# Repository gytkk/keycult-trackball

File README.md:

# keycult-trackball

Keycult No.1/60의 기존 케이스를 가공하지 않고 PCB와 알루미늄 보강판을 교체해 G/H 사이에 34mm 트랙볼을 통합하는 개인 프로젝트입니다. 제작 시제품은 cocot36plus를 참고한 베어링 롤러와 수평 PMW3360 모듈, 62키 직교 배열을 사용합니다. 유선 USB에서 키보드와 포인팅 장치를 함께 처리하는 QMK 펌웨어를 빌드했으며 실물 동작은 아직 시험하지 않았습니다.

현재 작업 위치는 비공개 독립 저장소 [gytkk/keycult-trackball](https://github.com/gytkk/keycult-trackball)입니다. 명령은 이 저장소 루트에서 실행합니다. 공개 선행 저장소 [gytkk/keycult-ball](https://github.com/gytkk/keycult-ball)은 별도로 유지하며 이 프로젝트의 변경을 그곳에 푸시하지 않습니다.

모노레포의 `8649717d63becea25a07a4f4efe33436537c2d38` 시점 산출물과 프로젝트 전용 변경 이력을 이전했습니다. 최초 파일 반입 트리가 선행 저장소의 `e3069346080183b74a5486131bdb68340fdf376d` 트리와 같아 해당 원본 이력에 후속 변경을 연결했습니다. 원본 추출 이력은 `archive/monorepo-extraction`, 선행 저장소 기준점은 `archive/keycult-ball-main` 브랜치에 보존합니다. 기존 이슈 링크는 선행 저장소의 기록을 가리키며 생성 보고서의 과거 절대 경로도 출처 기록으로 유지합니다.

현재 개발 우선안은 **62키 배열과 알루미늄 보강판**입니다. 65키안은 비교용으로 유지합니다. 시제품은 1.5mm 6061-T6 알루미늄 판재와 버 제거를 선택하며 가공 공차와 실제 강성은 검증이 필요합니다. [중앙 PCB 개구 검토](design/preliminary/design.md#중앙-pcb-개구와-알루미늄-보강판)에서 제조 방식과 남은 설계 조건을 설명합니다.

[출력용 홀더 시제품](design/printable-holder/README.md)은 **PCB 아래 0.82mm까지만 공간이 있다는 가정**으로 설계합니다. 이는 짧은 Mill-Max 3305-0의 명목 돌출을 참고한 사용자 요청이며 실제 케이스 측정값이 아닙니다. 받침을 보강판 위에 놓고 센서를 올려, 나사까지 포함한 하부 돌출을 PCB 아래 0.4mm로 제한합니다. 볼 중심은 보강판 위 23.5mm, 위끝은 40.5mm이므로 높은 볼의 사용성은 출력 후 확인해야 합니다. 상부 링은 없으며 볼을 위로 들어낼 수 있습니다. [단면도](design/preliminary/section.png)와 [치수 근거](design/preliminary/sources/README.md#shallow-clearance-reference)를 함께 확인합니다.

62키 DRAFT H는 모든 실장 전자부품을 PCB 윗면으로 옮기고 중앙 뒤쪽에 MCU, 전원과 커넥터를 배치합니다. 48 x 48mm R1 중앙 PCB 개구, 36 x 36mm R3 보강판 창과 42mm 체결 피치를 사용합니다. [PCB 안내](design/pcb/README.md)의 Gerber, PTH/NPTH 드릴, BOM과 실장 좌표는 시제품 제작 검토용이며 [검증 보고서](design/pcb/62/reports/validation.json)와 같은 원본에서 생성합니다. [펌웨어 안내](firmware/README.md)에 실제 UF2 빌드 결과와 입력 기능, 재현 및 초기 전원 시험 조건이 있습니다. 출력물, 실제 센서, 케이블과 케이스를 함께 조립한 검증은 남아 있습니다.

보유 케이스는 NovelKeys 최신 판매 버전의 WK이며 정확한 리비전과 과거 공식 보강판 윤곽의 호환성은 확인이 필요합니다. 이번 시제품의 장치와 배열은 cocot 방식과 62키로 선택했습니다. [과거 대안 조사](docs/feasibility.md)는 참고 자료로 유지하며 실제 장착 공간을 대신하지 않습니다.

현재 홀더에 맞춘 보강판과 조립 CAD는 [홀더 안내](design/printable-holder/README.md)와 [재현 절차](docs/reproduction.md#출력용-독립-홀더-시제품)를 따릅니다. 공식 NoLeaf 외곽을 포함하는 STEP/DXF/FCStd는 `design/preliminary/sources/local/`에만 생성합니다. 공개 홀더 CAD의 직사각형 `CandidatePlate`는 실제 Keycult 가공용 보강판이 아닙니다. 이전 65키 및 깊은 62키 보강판 검토는 과거 비교용입니다.

[케이스를 포함한 FreeCAD 참조 모델](design/preliminary/design.md#케이스-참조-모델)은 기존 홀더 검토 사본에 공개 외장 치수와 가정한 내부 형상을 추가합니다. 65키와 62키의 반투명 전체 보기, 절개 보기와 객체별 간섭 결과를 로컬에 생성하며 [실행 방법](docs/reproduction.md#케이스-참조-형상을-포함한-freecad-검토)을 따릅니다. 실제 케이스 내부와 보강판 정렬은 실측하지 않았으므로 참조 모델의 간섭 결과를 실물 조립 판정으로 사용하지 않습니다.

## 현재 검토 중인 배치

우선안은 15u 너비의 5행 62키 배열이며, 중앙 3열의 위쪽 4행을 비워 트랙볼과 뒤쪽 센서 공간을 확보합니다. 하단 중앙은 1.5u M1/M2 두 키로 총 3u를 차지하며 M3 물리 키는 제거합니다. 실제 키캡과 스위치 조립 적합성은 미확정입니다. 아래 값은 현재 예비 설계의 계산값입니다.

| 항목 | 값 또는 조건 |
| --- | --- |
| 키 피치와 명목 키필드 | 19.05mm, 285.75 × 95.25mm |
| 볼과 G/H 키 중심 | 볼 `(0, 0)`, G `(-38.10, 0)`, H `(+38.10, 0)`, 단위 mm |
| 볼과 키캡 사이 최소 평면 간격 | 지름 34mm 볼과 1u 18 x 18mm, 1.5u 27.525 x 18mm 키캡 가정에서 12.10mm |
| 임시 조립 예약 영역 | 50 × 50mm, 키캡과 최소 4.10mm 간격 |
| 개발 우선안 | 15u 62키. 65키안의 상단 중앙 Vol-/Mute/Vol+를 제거해 중앙 명목 빈 영역을 57.15 × 76.20mm로 확장 |
| 보류한 대안 | 14u 너비의 64키 배열. 같은 예약 영역과 키캡이 5.425mm 겹침 |

62키안은 볼 지름 34mm와 중심, G/H 및 하단 1.5u M1/M2를 포함한 나머지 키를 유지합니다. 뒤쪽 한 행을 비워 센서와 배선, 지지 브리지와 체결 간격을 검토할 공간을 확보합니다. 키 제거만으로 강성이 좋아지는 것은 아니며, 빈 영역 전체를 절개하면 강성이 낮아질 수 있습니다. 볼 지름은 65키안과 같지만 현재 62키 홀더의 하부 센서 공간은 별도로 검토합니다.

KiCad 원본은 비교용 65키의 `design/pcb/keycult65.*`와 제작 시제품 62키의 `design/pcb/62/keycult62.*`로 나눕니다. 62키는 윗면 전자부품을 뒤쪽 중앙 빈 영역에 배치하며 중앙 개구에서 0.25mm 확장한 영역을 구리와 부품 금지 영역으로 사용합니다. 개구, 높이와 커넥터는 시제품 설계값이며 실제 센서 및 케이스와 대조해야 합니다. 키 좌표는 예비 배치, PCB와 펌웨어가 공유합니다.

50 × 50mm 영역은 실제 홀더 외곽이나 보강판 및 PCB의 가공 구멍 치수가 아닙니다. 공개 도면의 초록색 경계도 공식 보강판 윤곽을 복제한 것이 아니라, 전체 치수만 참조한 285.75 × 108.25mm 직사각형입니다. 현재 검증은 이 경계 안의 포함 여부와 부품 사이 평면 간격을 확인하며, 실제 케이스 개구부 통과나 수직 공간, 조립 가능 여부를 증명하지 않습니다.

## 자료 안내

| 자료 | 내용 |
|---|---|
| [프로젝트 맥락](docs/project-context.md) | 요구사항, 결정 이유, 확정/가정/미확정, 실측·다음 단계 |
| [KiCad 65키·62키 초안](design/pcb/README.md) | 각 배열의 편집 가능한 회로도·PCB, BOM·GPIO 맵, 실제 ERC/DRC·좌표 검증 및 PDF/SVG |
| [PCB 구현 계획](docs/pcb-implementation-plan.md) | 실측 전에 진행할 회로도·PCB 초안, 단계별 산출물과 제조 전 검증 |
| [62키 QMK 펌웨어](firmware/README.md) | 빌드한 UF2, 고정된 소스, 버튼과 스크롤 기능, 재현 및 초기 동작 시험 |
| [실현 가능성과 대안 조사](docs/feasibility.md) | 34mm 중앙 통합의 제약과 중앙에 통합할 소형 터치패드·트랙볼 비교 |
| [상세 설계와 출처](design/preliminary/design.md) | 치수 계산, 장착·flex, 센서 방향, QMK·USB 범위 |
| [Ploopy / Keyball / Charybdis 및 라이선스](docs/alternatives-and-licenses.md) | 제품별 차이, 원본 공개 범위와 재사용 조건 |
| [배치 HTML](design/preliminary/layout.html) · [SVG](design/preliminary/layout.svg) · [JSON](design/preliminary/layout.json) | 브라우저 설명도, 편집 가능한 벡터, 모든 키 중심 좌표 |
| [단면 SVG](design/preliminary/section.svg) · [PNG](design/preliminary/section.png) | 62키 하부 수평 센서와 미확정 Z 스택 |
| [1:1 A3 PDF](design/preliminary/print-1to1.pdf) · [SVG](design/preliminary/print-1to1.svg) | 100mm 기준선 포함 종이 검증용 |
| [62키 옵션 SVG](design/preliminary/rear-clearance.svg) · [PNG](design/preliminary/rear-clearance.png) · [1:1 A3 PDF](design/preliminary/rear-clearance-print.pdf) · [인쇄 SVG](design/preliminary/rear-clearance-print.svg) · [인쇄 HTML](design/preliminary/rear-clearance-print.html) | 뒤쪽 공간 확보 비교. 좌표는 `layout.json`의 `rear_clearance` |
| [재현·검증 방법](docs/reproduction.md) | 좌표 생성, PNG/PDF 렌더, 원본 취득·해시 검증 |
| [에이전트 작업 지침](AGENTS.md) | 설계 변경, 검증, 공개 자료 관리, 커밋·푸시 규칙 |

HTML은 저장소를 내려받은 뒤 브라우저에서 엽니다. GitHub에서는 위 PNG로 미리 볼 수 있습니다. 종이 배치는 A3 가로, 배율 100%, 페이지 맞춤을 끈 상태로 출력하고 100mm 기준선을 자로 확인합니다.

## 생성과 검증

Python 3.11 이상과 `uv`를 사용하며, 명령은 이 저장소 루트에서 실행합니다. 검증 및 렌더 스크립트의 의존성은 각 파일의 메타데이터에 고정되어 있고 `uv run`이 준비합니다.

기존 산출물과 문서의 로컬 링크를 검증하려면 다음 명령을 실행합니다.

```bash
uv run scripts/validate.py
```

배열이나 치수를 변경한 경우에는 산출물을 순서대로 다시 생성하고 검증합니다.

```bash
uv run design/preliminary/build_artifacts.py
uv run scripts/render.py
uv run scripts/validate.py
```

`design/preliminary/build_artifacts.py`의 배열과 치수 상수가 편집 원본이며, 키 중심 JSON과 SVG/HTML은 생성 결과입니다. 설계 변경은 생성기에 반영합니다. 생성기만 실행하면 기존 PNG/PDF는 갱신되지 않으므로 `scripts/render.py`도 실행해야 합니다. 렌더에는 시스템 Chromium이 필요하며, PATH에서 찾을 수 없으면 `KEYCULT_CHROMIUM`에 실행 파일의 절대 경로를 지정합니다.

검증 스크립트는 파일 형식과 로컬 링크, 키 개수와 좌표, 평면 간격, 직사각형 경계 안의 포함 여부, PDF의 A3 크기와 100mm 기준선을 검사합니다. 검증 결과 일부는 `envelope-containment.json`과 `print-validation.json`에 기록됩니다.

공식 윤곽 검사는 별도 절차입니다. 원본 사용 조건을 확인한 뒤 `uv run scripts/fetch_sources.py`로 원본을 취득하고 `uv run scripts/verify_official_contour.py`로 재현합니다. [과거 검사 기록](design/preliminary/plate-containment.json)은 현재 공개 검증으로 갱신되지 않습니다. 추출 좌표와 재검사 출력의 저장 위치, 해시 확인 방법은 [재현 문서](docs/reproduction.md)를 따릅니다.

## 시제품 제작과 조립 순서

친구에게 PLA/FDM 시험 출력을 부탁할 때는 [출력 요청 패키지](design/print-request/README.md)를 사용합니다. [전달용 ZIP](design/print-request/keycult-print-request-PLA.zip)에는 기존 홀더, 중앙 시험판과 받침대, 높이별 센서 스페이서, PCB 개구 더미, 수량표와 존댓말 메일 초안이 있습니다. STL 13종을 예비분 포함 24개 출력하며, 실제 케이스용 보강판이나 최종 PA12 부품을 대신하지 않습니다.

1. [홀더 패키지](design/printable-holder/holder-PROTOTYPE.zip)의 시험편을 먼저 출력해 구멍과 체결을 확인한 뒤 본체를 출력합니다. 34mm 볼과 베어링을 조립하고 높은 볼의 접근성과 회전을 확인합니다. 출력 재질과 공차, 나사 및 센서의 세부 조건은 홀더 안내를 따릅니다.
2. 로컬 보강판 CAD를 실제 보강판과 대조하고, 케이스 바닥까지의 거리와 커넥터 및 케이블 통로를 확인합니다. PCB 아래 0.82mm는 설계 가정입니다. 납땜부, 스위치 핀, 절연재와 휨을 포함한 실제 여유를 확인하며 깊은 이전 홀더 파일을 혼용하지 않습니다.
3. [62키 PCB 제작 검토 패키지](design/pcb/README.md)를 업체와 검토합니다. 4층 stackup, USB 배선, QFN 노출 패드와 비아 처리, 부품 번호와 실장 방향을 확정한 뒤 시제품을 제작합니다. 실제 센서가 조건부 +3V3 인터페이스와 일치하는지도 확인합니다.
4. 센서를 연결하기 전에 전원 단락, 3.3V 전원과 USB 열거, 62키 입력을 시험합니다. 센서의 리비전과 케이블 도통을 확인한 뒤 연결하고 렌즈 높이, 축 방향, 클릭과 스크롤, USB 재연결 및 발열을 시험합니다. [펌웨어 안내](firmware/README.md)의 전원과 SROM 한계를 따릅니다.

측정할 항목과 결정 이유는 [프로젝트 맥락](docs/project-context.md)에 기록합니다. 예비 SVG를 제조용 도면으로 사용하지 않습니다.

## 범위와 출처 관리

공개 자료는 독립 키 배열, 형상을 복제하지 않는 요약 측정값, 검증 결과, 출처 URL과 해시입니다. 제3자 STEP/DXF/Gerber 원본, 공식 보강판 윤곽 좌표와 이를 복제한 도면은 공개하지 않습니다. 원본 다운로드는 `design/preliminary/sources/upstream/`에, 상세 윤곽과 로컬 검사 결과는 `design/preliminary/sources/local/`에 저장하며 두 디렉토리는 Git에서 제외합니다. 원본 대화, 개인 메모, 인증 정보도 포함하지 않습니다.

저장소 공개 자체가 제3자 자료의 재사용이나 재배포 허가를 뜻하지 않습니다. 자료를 취득하거나 재사용하기 전에 [자료별 라이선스와 배포 범위](docs/alternatives-and-licenses.md), [출처와 측정 기록](design/preliminary/sources/README.md)을 확인합니다.

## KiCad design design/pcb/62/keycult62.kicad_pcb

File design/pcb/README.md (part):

# Keycult65 and Keycult62 KiCad designs

**65-key DRAFT E and 62-key DRAFT H, not approved for fabrication or powered assembly.** Both variants use the same RP2040 circuit and stable key references. DRAFT H keeps the centred 48 x 48mm R1 opening and conditional Keyball module interface, moves every populated component to the top, and places the sensor above the main PCB on the raised cocot-inspired holder. Open the corresponding project in **KiCad 10.0.7**. The schematic and PCB are native editable CAD.

| Variant | Project | Schematic | PCB | Validation |
| --- | --- | --- | --- | --- |
| 65 keys | [keycult65.kicad_pro](keycult65.kicad_pro) | [Schematic](keycult65.kicad_sch) | [PCB](keycult65.kicad_pcb) | [Report](reports/validation.json) |
| 62 keys | [keycult62.kicad_pro](62/keycult62.kicad_pro) | [Schematic](62/keycult62.kicad_sch) | [PCB](62/keycult62.kicad_pcb) | [Report](62/reports/validation.json) |

Both variants pass strict native validation with zero ERC findings, DRC findings, unconnected items, schematic parity errors and independent netlist mismatches. The 62-key result follows fresh seed generation and saved SES replay, including local matrix, QSPI and power escape repairs recorded in its route manifest. The reports bind these results to the CAD hashes. Static electrical checks do not establish powered operation or case fit. The user-approved design assumption is an unmodified external UDB C5-JSH, represented by DB1 in the schematic and assembly BOM, with no footprint on the main PCB. J1 implements its 1:1 cable interface. The 62-key sensor interface uses the explicit draft assumption below; the actual module remains unidentified.

Historical DRAFT G preserved DRAFT F's nets and placements while shrinking the opening. DRAFT H replaces that 62-key placement and route to satisfy the shallow underside assumption. The 65-key CAD, exports and reports remain the delivered DRAFT E snapshot; shared-input hash refreshes do not change its geometry.

## Review entry points

- [Native schematic](keycult65.kicad_sch), [native PCB](keycult65.kicad_pcb), [project](keycult65.kicad_pro).
- [Schematic PDF](exports/schematic.pdf), [front copper SVG](exports/front.svg), [back copper SVG](exports/back.svg), [ground plane SVG](exports/ground.svg), [layer PDF](exports/board-layers.pdf).
- 62-key exports: [schematic PDF](62/exports/schematic.pdf), [front](62/exports/front.svg), [back](62/exports/back.svg), [ground plane](62/exports/ground.svg), [layer PDF](62/exports/board-layers.pdf), [BOM](62/bom.csv), [key/GPIO map](62/gpio-map.csv).
- [Real validation summary](reports/validation.json), [KiCad ERC](reports/erc.json), [KiCad DRC including native schematic parity](reports/drc.json), [actual exported netlist](reports/netlist.xml).
The layer PDF is auto-fitted for review, **not a 1:1 print or manufacturing template**.

- [BOM with candidates/uncertainties](bom.csv), [key/GPIO map](gpio-map.csv), [QMK pin reference](qmk-config.h.example), [source/license record](sources.md).

## Shallow 62-key prototype

DRAFT H uses the user's assumed clearance of 0.82mm below a nominal 1.6mm PCB, derived from the short Mill-Max 3305-0 reference rather than a case measurement. The switch footprints remain solder footprints. All 96 SMT parts, including the 62 diodes, are on F.Cu; the 62 switches remain top-mounted THT. Bottom test pads are copper features. Standard untrimmed MX leads project approximately 1.70mm below a 1.6mm PCB and exceed this assumption. All metal leads, plastic posts, solder and insulation must be trimmed or selected and physically checked against the 0.82mm limit. Top-side SMT placement alone is not a whole-board height pass.

The MCU, flash, power and service components occupy the empty rear central band. Diodes occupy the gaps between switch rows, with the bottom-row diodes offset horizontally from the preceding row. The copper/component reservation is now PCB x=155.75..204.25mm, y=75.75..124.25mm, a 0.25mm guard around the existing 48 x 48mm opening. It no longer reserves the entire empty key band. The 65-key snapshot keeps its original bottom electronics and central reservation.

J1 is now F.Cu, origin (153,64)mm, rotation 90 degrees; J2 is F.Cu, origin (177,58)mm, rotation 180 degrees. J1 has 0.825mm nominal clearance from the conservative 15.6mm switch proxy. Existing GND vias stay in place, with short F.Cu bridges to the moved pads; USB starts are shortened and a 1mm supply bridge preserves the power route. Their contact-number maps and external harness requirements are unchanged. Stock model heights above the mounting plane are 2.96mm for J1, 4.245mm for J2, 2.16mm for flash, 1.55mm for the LDO, 0.9mm for the MCU and 0.64mm for the crystal. These are library geometry, not supplied-part measurements. J2 needs the candidate plate's rear electronics relief because the PCB-top-to-plate-bottom gap is only 3.5mm. Connector insertion, cable routing and service-button access still need assembly inspection. The old J1 location and long USB route documented below apply to the 65-key DRAFT E snapshot.

The 62-key USB pair follows a short F.Cu route in the rear band with 0.29mm traces and a local 0.15mm D+ escape between the series-resistor pads. TP3 has a short B.Cu test branch; TP4 is accessed through a via. Ground stitches provide nearby returns. The uniform 0.29mm impedance estimate below does not qualify these local transitions or the cable. Read the current report for actual width, pair gap and reference-plane checks.

The [prototype CAM archive](62/keycult62-prototype-cam.zip) and [manifest](62/prototype-cam/manifest.json) contain four copper Gerbers, both masks, silkscreens and pastes, the outer/inner Edge.Cuts profile, separate PTH/NPTH Excellon drills, drill maps/report, the candidate BOM, all-component positions and top-SMT positions. The SMT file excludes test pads, external DB1 and THT switches. Coordinates are absolute mm; position CSV Y is positive upward, so PCB Y is negated. Bottom X is not mirrored. The assembler must approve native KiCad rotations and the QFN via/paste process.

Regenerate the bundle only after strict checks pass:

```bash
uv run --python "$(command -v python3)" scripts/validate_pcb.py --keys 62 --prototype-cam
```

Export checks compare all four copper X2 layer functions, drill-hit counts and placement references/positions/rotations/sides against the native PCB. The manifest binds CAM and CAD hashes and lists the remaining gates. Its stackup records F.Cu / In1.Cu / In2.Cu / B.Cu in order, material and dielectric constants. The copper/dielectric sum is 1.5862mm against nominal 1.6mm; mask construction and finish remain unspecified. The Gerber job's size includes the profile stroke, so use the native 285.0 x 94.6mm outline dimensions. This bundle permits local prototype review; it does not authorize an order or establish manufacturer approval.

## Implemented electrical content

65 or 62 MX PCB-mount solder switches and individual 1N4148W diodes. Cathode/pad 1 is
the ROW net; current path is COL → switch → diode anode → cathode → ROW. QMK
`COL2ROW`, five rows × fifteen columns; ten intersections are absent in the 65-key variant and thirteen in the 62-key variant. IDs, not labels, identify keys because labels repeat.

Both variants omit bottom-row SW59/D59 and retain SW58/D58 and SW60/D60 as the 1.5u M1/M2 keys, preserving IDs r4c6/r4c8 and removing r4c7. Their layout centres are (-14.2875,38.1)mm and (14.2875,38.1)mm. The 62-key variant also omits SW7-SW9 and D7-D9 without renumbering other parts. COL6 and COL8 remain connected to the bottom keys; COL7 has no key, so GP16 is NC. The [compiled prototype firmware](../../firmware/README.md) uses `NO_PIN` for that column, `KC_NO` for absent cells, M1/M2 for mouse buttons and Fn+M1 for middle click. Cutting a populated older PCB is never implied by removing switches.

RP2040 is directly mounted in its 7×7mm QFN, not represented by a development
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
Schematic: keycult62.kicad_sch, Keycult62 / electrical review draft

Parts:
C1, C2: 1uF; C_0603_1608Metric
C3, C4, C5, C6, C7, C8, C9, C10, C11, C12, C15: 100nF; C_0402_1005Metric
C13, C14: 1uF; C_0402_1005Metric
C16, C17: 15pF; C_0402_1005Metric
D1, D2, D3, D4, D5, D6, D10, D11, D12, D13, D14, D15, D16, D17, D18, D19, D20, D21, D22, D23, D24, D25, D26, D27, D28, D29, D30, D31, D32, D33, D34, D35, D36, D37, D38, D39, D40, D41, D42, D43, D44, D45, D46, D47, D48, D49, D50, D51, D52, D53, D54, D55, D56, D57, D58, D60, D61, D62, D63, D64, D65, D66: 1N4148W; D_SOD-123
DB1: UDB C5-JSH / EXTERNAL
F1: 500mA hold / provisional; Fuse_0805_2012Metric
J1: USB / C5-JSH JST-SH; JST_SH_SM04B-SRSS-TB_1x04-1MP_P1.00mm_Horizontal
J2: KEYBALL / 3V3 ASSUMED; JST_GH_SM07B-GHS-TB_1x07-1MP_P1.25mm_Horizontal
R1, R2, R7: 27R; R_0402_1005Metric
R3, R5, R8: 10k; R_0402_1005Metric
R4, R6: 1k; R_0402_1005Metric
SW1: r0c0 Esc; SW_Cherry_MX_1.00u_PCB
SW2: r0c1 1; SW_Cherry_MX_1.00u_PCB
SW3: r0c2 2; SW_Cherry_MX_1.00u_PCB
SW4: r0c3 3; SW_Cherry_MX_1.00u_PCB
SW5: r0c4 4; SW_Cherry_MX_1.00u_PCB
SW6: r0c5 5; SW_Cherry_MX_1.00u_PCB
SW10: r0c9 6; SW_Cherry_MX_1.00u_PCB
SW11: r0c10 7; SW_Cherry_MX_1.00u_PCB
SW12: r0c11 8; SW_Cherry_MX_1.00u_PCB
SW13: r0c12 9; SW_Cherry_MX_1.00u_PCB
SW14: r0c13 0; SW_Cherry_MX_1.00u_PCB
SW15: r0c14 Bksp; SW_Cherry_MX_1.00u_PCB
SW16: r1c0 Tab; SW_Cherry_MX_1.00u_PCB
SW17: r1c1 Q; SW_Cherry_MX_1.00u_PCB
SW18: r1c2 W; SW_Cherry_MX_1.00u_PCB
SW19: r1c3 E; SW_Cherry_MX_1.00u_PCB
SW20: r1c4 R; SW_Cherry_MX_1.00u_PCB
SW21: r1c5 T; SW_Cherry_MX_1.00u_PCB
SW22: r1c9 Y; SW_Cherry_MX_1.00u_PCB
SW23: r1c10 U; SW_Cherry_MX_1.00u_PCB
SW24: r1c11 I; SW_Cherry_MX_1.00u_PCB
SW25: r1c12 O; SW_Cherry_MX_1.00u_PCB
SW26: r1c13 P; SW_Cherry_MX_1.00u_PCB
SW27: r1c14 \; SW_Cherry_MX_1.00u_PCB
SW28: r2c0 Caps; SW_Cherry_MX_1.00u_PCB
SW29: r2c1 A; SW_Cherry_MX_1.00u_PCB
SW30: r2c2 S; SW_Cherry_MX_1.00u_PCB
SW31: r2c3 D; SW_Cherry_MX_1.00u_PCB
SW32: r2c4 F; SW_Cherry_MX_1.00u_PCB
SW33: r2c5 G; SW_Cherry_MX_1.00u_PCB
SW34: r2c9 H; SW_Cherry_MX_1.00u_PCB
SW35: r2c10 J; SW_Cherry_MX_1.00u_PCB
SW36: r2c11 K; SW_Cherry_MX_1.00u_PCB
SW37: r2c12 L; SW_Cherry_MX_1.00u_PCB
SW38: r2c13 ;; SW_Cherry_MX_1.00u_PCB
SW39: r2c14 Enter; SW_Cherry_MX_1.00u_PCB
SW40: r3c0 Shift; SW_Cherry_MX_1.00u_PCB
SW41: r3c1 Z; SW_Cherry_MX_1.00u_PCB
SW42: r3c2 X; SW_Cherry_MX_1.00u_PCB
SW43: r3c3 C; SW_Cherry_MX_1.00u_PCB
SW44: r3c4 V; SW_Cherry_MX_1.00u_PCB
SW45: r3c5 B; SW_Cherry_MX_1.00u_PCB
SW46: r3c9 N; SW_Cherry_MX_1.00u_PCB
SW47: r3c10 M; SW_Cherry_MX_1.00u_PCB
SW48: r3c11 ,; SW_Cherry_MX_1.00u_PCB
SW49: r3c12 .; SW_Cherry_MX_1.00u_PCB
SW50: r3c13 /; SW_Cherry_MX_1.00u_PCB
SW51: r3c14 Shift; SW_Cherry_MX_1.00u_PCB
SW52: r4c0 Ctrl; SW_Cherry_MX_1.00u_PCB
SW53: r4c1 GUI; SW_Cherry_MX_1.00u_PCB
SW54: r4c2 Alt; SW_Cherry_MX_1.00u_PCB
SW55: r4c3 Fn; SW_Cherry_MX_1.00u_PCB
SW56: r4c4 Space; SW_Cherry_MX_1.00u_PCB
SW57: r4c5 Del; SW_Cherry_MX_1.00u_PCB
SW58: r4c6 M1; SW_Cherry_MX_1.50u_PCB
SW60: r4c8 M2; SW_Cherry_MX_1.50u_PCB
SW61: r4c9 Bksp; SW_Cherry_MX_1.00u_PCB
SW62: r4c10 Space; SW_Cherry_MX_1.00u_PCB
SW63: r4c11 Fn; SW_Cherry_MX_1.00u_PCB
SW64: r4c12 Left; SW_Cherry_MX_1.00u_PCB
SW65: r4c13 Down; SW_Cherry_MX_1.00u_PCB
SW66: r4c14 Right; SW_Cherry_MX_1.00u_PCB
SW67: BOOTSEL; SW_SPST_TL3342
SW68: RESET; SW_SPST_TL3342
TP1: VBUS_USB / USB TEST; TestPoint_Pad_D1.5mm
TP2: GND / USB TEST; TestPoint_Pad_D1.5mm
TP3: USB_DM / USB TEST; TestPoint_Pad_D1.5mm
TP4: USB_DP / USB TEST; TestPoint_Pad_D1.5mm
TP5: SWCLK / SWD; TestPoint_Pad_D1.0mm
TP6: SWDIO / SWD; TestPoint_Pad_D1.0mm
TP7: RUN / SWD; TestPoint_Pad_D1.0mm
TP8: GND / SWD; TestPoint_Pad_D1.0mm
TP9: +3V3 / SWD; TestPoint_Pad_D1.0mm
TP10: SENSOR_MISO_3V3; TestPoint_Pad_D1.0mm
TP11: SENSOR_CS_3V3; TestPoint_Pad_D1.0mm
TP12: SENSOR_SCLK_3V3; TestPoint_Pad_D1.0mm
TP13: SENSOR_MOSI_3V3; TestPoint_Pad_D1.0mm
TP14: SENSOR_MOTION_3V3; TestPoint_Pad_D1.0mm
TP15: SENSOR_RESET_3V3; TestPoint_Pad_D1.0mm
TP16: GND; TestPoint_Pad_D1.0mm
TP17: +3V3; TestPoint_Pad_D1.0mm
U1: RP2040; QFN-56-1EP_7x7mm_P0.4mm_EP3.2x3.2mm
U2: W25Q16JVSSIQ; SOIC-8_5.3x5.3mm_P1.27mm
U3: AP2112K-3.3TRG1; SOT-23-5
Y1: ABM8-272-T3 12MHz CL10pF; Crystal_SMD_3225-4Pin_3.2x2.5mm

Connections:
+1V1: C11.1, C12.1, C14.1, U1.23 (DVDD), U1.45 (VREG_VOUT), U1.50 (DVDD)
+3V3: C2.1, C3.1, C4.1, C5.1, C6.1, C7.1, C8.1, C9.1, C10.1, C13.1, C15.1, J2.4, R3.1, R5.1, R8.1, TP9.1, TP17.1, U1.1 (IOVDD), U1.10 (IOVDD), U1.22 (IOVDD), U1.33 (IOVDD), U1.42 (IOVDD), U1.43 (ADC_AVDD), U1.44 (VREG_VIN), U1.48 (USB_VDD), U1.49 (IOVDD), U2.8 (VCC), U3.5 (VOUT)
BOOT_SW: R4.2, SW67.1
COL0: SW1.1, SW16.1, SW28.1, SW40.1, SW52.1, U1.12 (GPIO9)
COL1: SW2.1, SW17.1, SW29.1, SW41.1, SW53.1, U1.13 (GPIO10)
COL2: SW3.1, SW18.1, SW30.1, SW42.1, SW54.1, U1.14 (GPIO11)
COL3: SW4.1, SW19.1, SW31.1, SW43.1, SW55.1, U1.15 (GPIO12)
COL4: SW5.1, SW20.1, SW32.1, SW44.1, SW56.1, U1.16 (GPIO13)
COL5: SW6.1, SW21.1, SW33.1, SW45.1, SW57.1, U1.17 (GPIO14)
COL6: SW58.1, U1.18 (GPIO15)
COL8: SW60.1, U1.28 (GPIO17)
COL9: SW10.1, SW22.1, SW34.1, SW46.1, SW61.1, U1.29 (GPIO18)
COL10: SW11.1, SW23.1, SW35.1, SW47.1, SW62.1, U1.30 (GPIO19)
COL11: SW12.1, SW24.1, SW36.1, SW48.1, SW63.1, U1.31 (GPIO20)
COL12: SW13.1, SW25.1, SW37.1, SW49.1, SW64.1, U1.32 (GPIO21)
COL13: SW14.1, SW26.1, SW38.1, SW50.1, SW65.1, U1.34 (GPIO22)
COL14: SW15.1, SW27.1, SW39.1, SW51.1, SW66.1, U1.38 (GPIO26/ADC0)
GND: C1.2, C2.2, C3.2, C4.2, C5.2, C6.2, C7.2, C8.2, C9.2, C10.2, C11.2, C12.2, C13.2, C14.2, C15.2, C16.2, C17.2, DB1.4, J1.4, J1.MP (MountPin), J2.3, J2.5, J2.MP (MountPin), SW67.2, SW68.2, TP2.1, TP8.1, TP16.1, U1.19 (TESTEN), U1.57 (GND), U2.4 (GND), U3.2 (GND), Y1.2 (G), Y1.4 (G)
K_r0c0: D1.2 (A), SW1.2
K_r0c1: D2.2 (A), SW2.2
K_r0c2: D3.2 (A), SW3.2
K_r0c3: D4.2 (A), SW4.2
K_r0c4: D5.2 (A), SW5.2
K_r0c5: D6.2 (A), SW6.2
K_r0c9: D10.2 (A), SW10.2
K_r0c10: D11.2 (A), SW11.2
K_r0c11: D12.2 (A), SW12.2
K_r0c12: D13.2 (A), SW13.2
K_r0c13: D14.2 (A), SW14.2
K_r0c14: D15.2 (A), SW15.2
K_r1c0: D16.2 (A), SW16.2
K_r1c1: D17.2 (A), SW17.2
K_r1c2: D18.2 (A), SW18.2
K_r1c3: D19.2 (A), SW19.2
K_r1c4: D20.2 (A), SW20.2
K_r1c5: D21.2 (A), SW21.2
K_r1c9: D22.2 (A), SW22.2
K_r1c10: D23.2 (A), SW23.2
K_r1c11: D24.2 (A), SW24.2
K_r1c12: D25.2 (A), SW25.2
K_r1c13: D26.2 (A), SW26.2
K_r1c14: D27.2 (A), SW27.2
K_r2c0: D28.2 (A), SW28.2
K_r2c1: D29.2 (A), SW29.2
K_r2c2: D30.2 (A), SW30.2
K_r2c3: D31.2 (A), SW31.2
K_r2c4: D32.2 (A), SW32.2
K_r2c5: D33.2 (A), SW33.2
K_r2c9: D34.2 (A), SW34.2
K_r2c10: D35.2 (A), SW35.2
K_r2c11: D36.2 (A), SW36.2
K_r2c12: D37.2 (A), SW37.2
K_r2c13: D38.2 (A), SW38.2
K_r2c14: D39.2 (A), SW39.2
K_r3c0: D40.2 (A), SW40.2
K_r3c1: D41.2 (A), SW41.2
K_r3c2: D42.2 (A), SW42.2
K_r3c3: D43.2 (A), SW43.2
K_r3c4: D44.2 (A), SW44.2
K_r3c5: D45.2 (A), SW45.2
K_r3c9: D46.2 (A), SW46.2
K_r3c10: D47.2 (A), SW47.2
K_r3c11: D48.2 (A), SW48.2
K_r3c12: D49.2 (A), SW49.2
K_r3c13: D50.2 (A), SW50.2
K_r3c14: D51.2 (A), SW51.2
K_r4c0: D52.2 (A), SW52.2
K_r4c1: D53.2 (A), SW53.2
K_r4c2: D54.2 (A), SW54.2
K_r4c3: D55.2 (A), SW55.2
K_r4c4: D56.2 (A), SW56.2
K_r4c5: D57.2 (A), SW57.2
K_r4c6: D58.2 (A), SW58.2
K_r4c8: D60.2 (A), SW60.2
K_r4c9: D61.2 (A), SW61.2
K_r4c10: D62.2 (A), SW62.2
K_r4c11: D63.2 (A), SW63.2
K_r4c12: D64.2 (A), SW64.2
K_r4c13: D65.2 (A), SW65.2
K_r4c14: D66.2 (A), SW66.2
QSPI_SCLK: R7.1, U1.52 (QSPI_SCLK)
QSPI_SCLK_FLASH: R7.2, U2.6 (CLK)
QSPI_SD0: U1.53 (QSPI_SD0), U2.5 (DI/IO_{0})
QSPI_SD1: U1.55 (QSPI_SD1), U2.2 (DO/IO_{1})
QSPI_SD2: U1.54 (QSPI_SD2), U2.3 (~WP/IO_{2})
QSPI_SD3: U1.51 (QSPI_SD3), U2.7 (~HOLD/~RESET/IO_{3})
QSPI_SS: R3.2, R4.1, U1.56 (~QSPI_SS), U2.1 (~CS)
ROW0: D1.1 (K), D2.1 (K), D3.1 (K), D4.1 (K), D5.1 (K), D6.1 (K), D10.1 (K), D11.1 (K), D12.1 (K), D13.1 (K), D14.1 (K), D15.1 (K), U1.6 (GPIO4)
ROW1: D16.1 (K), D17.1 (K), D18.1 (K), D19.1 (K), D20.1 (K), D21.1 (K), D22.1 (K), D23.1 (K), D24.1 (K), D25.1 (K), D26.1 (K), D27.1 (K), U1.7 (GPIO5)
ROW2: D28.1 (K), D29.1 (K), D30.1 (K), D31.1 (K), D32.1 (K), D33.1 (K), D34.1 (K), D35.1 (K), D36.1 (K), D37.1 (K), D38.1 (K), D39.1 (K), U1.8 (GPIO6)
ROW3: D40.1 (K), D41.1 (K), D42.1 (K), D43.1 (K), D44.1 (K), D45.1 (K), D46.1 (K), D47.1 (K), D48.1 (K), D49.1 (K), D50.1 (K), D51.1 (K), U1.9 (GPIO7)
ROW4: D52.1 (K), D53.1 (K), D54.1 (K), D55.1 (K), D56.1 (K), D57.1 (K), D58.1 (K), D60.1 (K), D61.1 (K), D62.1 (K), D63.1 (K), D64.1 (K), D65.1 (K), D66.1 (K), U1.11 (GPIO8)
RUN: R5.2, SW68.1, TP7.1, U1.26 (RUN)
SENSOR_CS_3V3: J2.2, R8.2, TP11.1, U1.3 (GPIO1)
SENSOR_MISO_3V3: J2.7, TP10.1, U1.2 (GPIO0)
SENSOR_MOSI_3V3: J2.6, TP13.1, U1.5 (GPIO3)
SENSOR_MOTION_3V3: TP14.1, U1.35 (GPIO23)
SENSOR_RESET_3V3: TP15.1, U1.36 (GPIO24)
SENSOR_SCLK_3V3: J2.1, TP12.1, U1.4 (GPIO2)
SWCLK: TP5.1, U1.24 (SWCLK)
SWDIO: TP6.1, U1.25 (SWDIO)
USB_DM: DB1.2, J1.2, R1.2, TP3.1
USB_DM_MCU: R1.1, U1.46 (USB_DM)
USB_DP: DB1.3, J1.3, R2.2, TP4.1
USB_DP_MCU: R2.1, U1.47 (USB_DP)
VBUS_FUSED: C1.1, F1.2, U3.1 (VIN), U3.3 (EN)
VBUS_USB: DB1.1, F1.1, J1.1, TP1.1
XIN: C16.1, U1.20 (XIN), Y1.1
XOUT: R6.1, U1.21 (XOUT)
XOUT_CRYSTAL: C17.1, R6.2, Y1.3

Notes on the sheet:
1 / RP2040 + FLASH + BOOT + RESET
2 / USB DAUGHTERBOARD + 3V3 POWER
3 / CLOCK + SENSOR 3V3 CABLE INTERFACE
J2: 3V3 ONLY. Published Keyball46 circuit assumed; module identity/current/timing NOT qualified.
DECOUPLING: individual IOVDD / USB / ADC / DVDD pins; VREG 1uF input + output
4 / 5 ROW x 15 COLUMN MATRIX: COL -> switch -> diode ANODE -> CATHODE -> ROW (COL2ROW)
62 keys; Keycult62. Bottom M1/M2: 1.5u each. PCB opening 48x60 R1 assumed; holder fit UNVERIFIED.
DB1: EXTERNAL C5-JSH assumed; CC 5.1k x2 / TPD4E05U06 ESD / PTC / SMF6.0A TVS.
J1: 1=protected USB power 2=D- 3=D+ 4=GND; 1:1 cable. Main-board F1 retained.
Shield joins GND on DB1. No active sustained-overvoltage disconnect. Mechanical fit provisional.

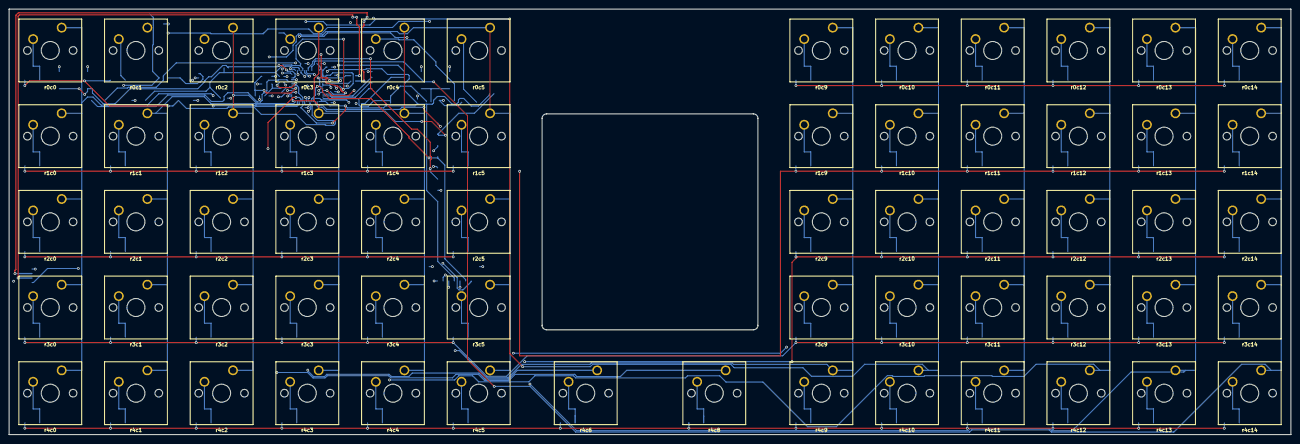
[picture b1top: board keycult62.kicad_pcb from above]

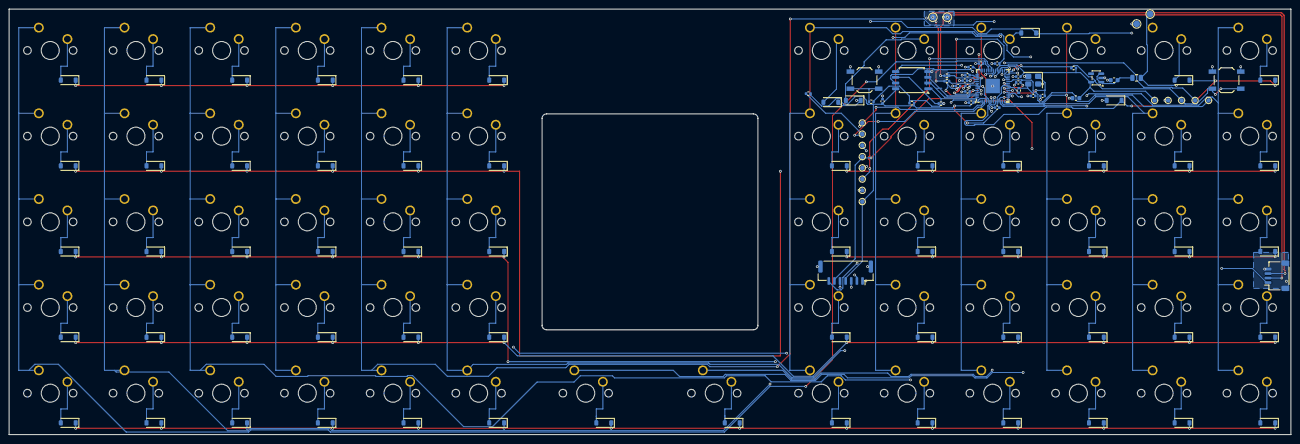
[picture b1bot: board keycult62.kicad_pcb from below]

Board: 4 copper layers, 285.0 x 94.6 mm, 175 parts (113 on the bottom side), 110 nets.

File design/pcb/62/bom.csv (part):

Reference,Value,Manufacturer part / candidate,Footprint,Assembly,Status,Notes
U1,RP2040,RP2040,Package_DFN_QFN:QFN-56-1EP_7x7mm_P0.4mm_EP3.2x3.2mm,Bottom SMT,provisional sourcing,Direct mounted QFN; exposed pad to GND; unused GP25/27/28/29 NC
U2,W25Q16JVSSIQ,W25Q16JVSSIQ,Package_SO:SOIC-8_5.3x5.3mm_P1.27mm,Bottom SMT,provisional sourcing,"208 mil SOIC, NOT 150mil package; QMK RP2040 flash boot stage must match"
U3,AP2112K-3.3TRG1,AP2112K-3.3TRG1,Package_TO_SOT_SMD:SOT-23-5,Bottom SMT,provisional sourcing,600mA part rating is NOT USB budget; 5V->3V3 thermal/load budget unresolved
J1,USB / C5-JSH JST-SH,JST SM04B-SRSS-TB(LF)(SN),Connector_JST:JST_SH_SM04B-SRSS-TB_1x04-1MP_P1.00mm_Horizontal,Bottom SMT,C5-JSH interface selected; mechanical fit provisional,"1 protected USB power, 2 D-, 3 D+, 4 GND; 1:1 JST-SH cable of suitable length. External DB1 supplies CC/ESD/PTC/TVS; VBUS_USB is after its PTC and before main-board F1"
DB1,UDB C5-JSH / EXTERNAL,Unified Daughterboard C5-JSH,,External assembly,user-approved design assumption; external assembly,"Pinned 2b6c52aa2de6f9f60ca99c6250e4bdf01e8f4eea; 5.1k CC, TPD4E05U06DQAR ESD, ASMD1206-150 PTC, SMF6.0A TVS, direct shield/GND connection; no active sustained-overvoltage disconnect; not fitted on main PCB"
TP1,VBUS_USB / USB TEST,PCB pad,TestPoint:TestPoint_Pad_D1.5mm,Bottom SMT,test access; J1 is the cable connector,Test-pad numbering differs from J1 contact numbering
TP2,GND / USB TEST,PCB pad,TestPoint:TestPoint_Pad_D1.5mm,Bottom SMT,test access; J1 is the cable connector,Test-pad numbering differs from J1 contact numbering
TP3,USB_DM / USB TEST,PCB pad,TestPoint:TestPoint_Pad_D1.5mm,Bottom SMT,test access; J1 is the cable connector,Test-pad numbering differs from J1 contact numbering
TP4,USB_DP / USB TEST,PCB pad,TestPoint:TestPoint_Pad_D1.5mm,Bottom SMT,test access; J1 is the cable connector,Test-pad numbering differs from J1 contact numbering
F1,500mA hold / provisional,Bourns MF-PSMF050X-2,Fuse:Fuse_0805_2012Metric,Bottom SMT,provisional sourcing,"Retained local main-board PTC after C5-JSH PTC; total drop, load/inrush and trip coordination need verification; not a USB current entitlement"
C1,1uF,TBD X7R 10V,Capacitor_SMD:C_0603_1608Metric,Bottom SMT,provisional sourcing,voltage rating >=10V; capacitance under DC bias to verify
C2,1uF,TBD X7R 10V,Capacitor_SMD:C_0603_1608Metric,Bottom SMT,provisional sourcing,voltage rating >=10V; capacitance under DC bias to verify
C3,100nF,TBD X7R 10V,Capacitor_SMD:C_0402_1005Metric,Bottom SMT,provisional sourcing,voltage rating >=10V; capacitance under DC bias to verify; IOVDD1
C4,100nF,TBD X7R 10V,Capacitor_SMD:C_0402_1005Metric,Bottom SMT,provisional sourcing,voltage rating >=10V; capacitance under DC bias to verify; IOVDD10
C5,100nF,TBD X7R 10V,Capacitor_SMD:C_0402_1005Metric,Bottom SMT,provisional sourcing,voltage rating >=10V; capacitance under DC bias to verify; IOVDD22
C6,100nF,TBD X7R 10V,Capacitor_SMD:C_0402_1005Metric,Bottom SMT,provisional sourcing,voltage rating >=10V; capacitance under DC bias to verify; IOVDD33
C7,100nF,TBD X7R 10V,Capacitor_SMD:C_0402_1005Metric,Bottom SMT,provisional sourcing,voltage rating >=10V; capacitance under DC bias to verify; IOVDD42
C8,100nF,TBD X7R 10V,Capacitor_SMD:C_0402_1005Metric,Bottom SMT,provisional sourcing,voltage rating >=10V; capacitance under DC bias to verify; IOVDD49
C9,100nF,TBD X7R 10V,Capacitor_SMD:C_0402_1005Metric,Bottom SMT,provisional sourcing,voltage rating >=10V; capacitance under DC bias to verify; ADC_AVDD43
C10,100nF,TBD X7R 10V,Capacitor_SMD:C_0402_1005Metric,Bottom SMT,provisional sourcing,voltage rating >=10V; capacitance under DC bias to verify; USB_VDD48
C11,100nF,TBD X7R 10V,Capacitor_SMD:C_0402_1005Metric,Bottom SMT,provisional sourcing,voltage rating >=10V; capacitance under DC bias to verify; DVDD23
C12,100nF,TBD X7R 10V,Capacitor_SMD:C_0402_1005Metric,Bottom SMT,provisional sourcing,voltage rating >=10V; capacitance under DC bias to verify; DVDD50
C13,1uF,TBD X7R 10V,Capacitor_SMD:C_0402_1005Metric,Bottom SMT,provisional sourcing,voltage rating >=10V; capacitance under DC bias to verify; VREG_VIN44
C14,1uF,TBD X7R 10V,Capacitor_SMD:C_0402_1005Metric,Bottom SMT,provisional sourcing,voltage rating >=10V; capacitance under DC bias to verify; VREG_VOUT45
C15,100nF,TBD X7R 10V,Capacitor_SMD:C_0402_1005Metric,Bottom SMT,provisional sourcing,voltage rating >=10V; capacitance under DC bias to verify; QSPI flash VCC
R1,27R,TBD 0402 1% 50V,Resistor_SMD:R_0402_1005Metric,Bottom SMT,provisional sourcing,value fixed; manufacturer not selected
R2,27R,TBD 0402 1% 50V,Resistor_SMD:R_0402_1005Metric,Bottom SMT,provisional sourcing,value fixed; manufacturer not selected
R3,10k,TBD 0402 1% 50V,Resistor_SMD:R_0402_1005Metric,Bottom SMT,provisional sourcing,value fixed; manufacturer not selected
R4,1k,TBD 0402 1% 50V,Resistor_SMD:R_0402_1005Metric,Bottom SMT,provisional sourcing,value fixed; manufacturer not selected
R5,10k,TBD 0402 1% 50V,Resistor_SMD:R_0402_1005Metric,Bottom SMT,provisional sourcing,value fixed; manufacturer not selected
R6,1k,TBD 0402 1% 50V,Resistor_SMD:R_0402_1005Metric,Bottom SMT,provisional sourcing,value fixed; manufacturer not selected
R7,27R,TBD 0402 1% 50V,Resistor_SMD:R_0402_1005Metric,Bottom SMT,provisional sourcing,value fixed; manufacturer not selected
Y1,ABM8-272-T3 12MHz CL10pF,ABM8-272-T3,Crystal:Crystal_SMD_3225-4Pin_3.2x2.5mm,Bottom SMT,provisional sourcing,Confirm ESR/drive/startup on assembled board
C16,15pF,TBD C0G 50V,Capacitor_SMD:C_0402_1005Metric,Bottom SMT,provisional sourcing,voltage rating >=10V; capacitance under DC bias to verify
C17,15pF,TBD C0G 50V,Capacitor_SMD:C_0402_1005Metric,Bottom SMT,provisional sourcing,voltage rating >=10V; capacitance under DC bias to verify
SW67,BOOTSEL,E-Switch TL3342F160QG,Button_Switch_SMD:SW_SPST_TL3342,Bottom SMT,provisional sourcing,Backside service access and switch height not mechanically verified
SW68,RESET,E-Switch TL3342F160QG,Button_Switch_SMD:SW_SPST_TL3342,Bottom SMT,provisional sourcing,Backside service access and switch height not mechanically verified
TP5,SWCLK / SWD,PCB pad,TestPoint:TestPoint_Pad_D1.0mm,Bottom SMT,electrically defined; access provisional,
TP6,SWDIO / SWD,PCB pad,TestPoint:TestPoint_Pad_D1.0mm,Bottom SMT,electrically defined; access provisional,
TP7,RUN / SWD,PCB pad,TestPoint:TestPoint_Pad_D1.0mm,Bottom SMT,electrically defined; access provisional,
TP8,GND / SWD,PCB pad,TestPoint:TestPoint_Pad_D1.0mm,Bottom SMT,electrically defined; access provisional,
TP9,+3V3 / SWD,PCB pad,TestPoint:TestPoint_Pad_D1.0mm,Bottom SMT,electrically defined; access provisional,
TP10,SENSOR_MISO_3V3,PCB pad,TestPoint:TestPoint_Pad_D1.0mm,Bottom SMT,3V3 MCU-side logical pads ONLY,"J2 exports SPI0/GND/3V3 under historical-module assumption; TP14/15 are spare motion/reset, not module contacts"
TP11,SENSOR_CS_3V3,PCB pad,TestPoint:TestPoint_Pad_D1.0mm,Bottom SMT,3V3 MCU-side logical pads ONLY,"J2 exports SPI0/GND/3V3 under historical-module assumption; TP14/15 are spare motion/reset, not module contacts"
TP12,SENSOR_SCLK_3V3,PCB pad,TestPoint:TestPoint_Pad_D1.0mm,Bottom SMT,3V3 MCU-side logical pads ONLY,"J2 exports SPI0/GND/3V3 under historical-module assumption; TP14/15 are spare motion/reset, not module contacts"
TP13,SENSOR_MOSI_3V3,PCB pad,TestPoint:TestPoint_Pad_D1.0mm,Bottom SMT,3V3 MCU-side logical pads ONLY,"J2 exports SPI0/GND/3V3 under historical-module assumption; TP14/15 are spare motion/reset, not module contacts"
TP14,SENSOR_MOTION_3V3,PCB pad,TestPoint:TestPoint_Pad_D1.0mm,Bottom SMT,3V3 MCU-side logical pads ONLY,"J2 exports SPI0/GND/3V3 under historical-module assumption; TP14/15 are spare motion/reset, not module contacts"
TP15,SENSOR_RESET_3V3,PCB pad,TestPoint:TestPoint_Pad_D1.0mm,Bottom SMT,3V3 MCU-side logical pads ONLY,"J2 exports SPI0/GND/3V3 under historical-module assumption; TP14/15 are spare motion/reset, not module contacts"
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
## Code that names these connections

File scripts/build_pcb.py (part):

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revision='H' if args.keys==62 else 'E'
ROW_GPIO=[4,5,6,7,8]; COL_GPIO=[9,10,11,12,13,14,15,16,17,18,19,20,21,22,26]
# Reserve hardware SPI0 GP0/1/2/3 before assigning the twenty matrix pins.
gpio={0:'SENSOR_MISO_3V3',1:'SENSOR_CS_3V3',2:'SENSOR_SCLK_3V3',3:'SENSOR_MOSI_3V3'}
gpio.update({n:f'ROW{i}' for i,n in enumerate(ROW_GPIO)})
gpio.update({n:f'COL{i}' for i,n in enumerate(COL_GPIO)})
if args.keys==62:gpio[COL_GPIO[7]]=None  # No switches remain in COL7 on this variant.
gpio.update({23:'SENSOR_MOTION_3V3',24:'SENSOR_RESET_3V3'})
u1={}
for p in pins('MCU_RaspberryPi:RP2040'):
    num=item(p,'number')[1]; name=item(p,'name')[1]
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res('R6','1k',('XOUT','XOUT_CRYSTAL'),(469.9,73.66),(186.5,71.8),90)
res('R7','27R',('QSPI_SCLK','QSPI_SCLK_FLASH'),(241.3,139.7),(188.2,66.1))
# 12MHz, CL=10pF; 15pF caps assume ~2.5pF parasitics and require oscillator bring-up.
part('Y1','Device:Crystal_GND24','ABM8-272-T3 12MHz CL10pF','Crystal:Crystal_SMD_3225-4Pin_3.2x2.5mm',{1:'XIN',2:'GND',3:'XOUT_CRYSTAL',4:'GND'},(520.7,73.66),(187.2,69),mpn='ABM8-272-T3',note='Confirm ESR/drive/startup on assembled board')
cap('C16','15pF','XIN',(500.38,116.84),(186.5,73.8))
cap('C17','15pF','XOUT_CRYSTAL',(541.02,116.84),(189,73.8))
for ref,net,x,schx in [('SW67','BOOT_SW',205.5,215.9),('SW68','RUN',165.5,139.7)]:
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
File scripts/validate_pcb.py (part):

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 coord.append({'id':k['id'],'switch':f'SW{i}','expected_stem_mm':expected,'actual_stem_mm':actual,'error_mm':delta})
netroot=ET.parse(R/'netlist.xml').getroot()
schnet={(n.attrib['ref'],n.attrib['pin']):net.attrib['name'].replace('/','{slash}') for net in netroot.find('nets') for n in net.findall('node')}
check({pin:net for (ref,pin),net in schnet.items() if ref=='DB1'}=={'1':'VBUS_USB','2':'USB_DM','3':'USB_DP','4':'GND'},'External C5-JSH netlist pinout differs from J1')
netdiff=[]
net_pad_counts=Counter(p.GetNetname() for f in fps.values() for p in f.Pads() if p.GetNumber())
for ref,f in fps.items():
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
